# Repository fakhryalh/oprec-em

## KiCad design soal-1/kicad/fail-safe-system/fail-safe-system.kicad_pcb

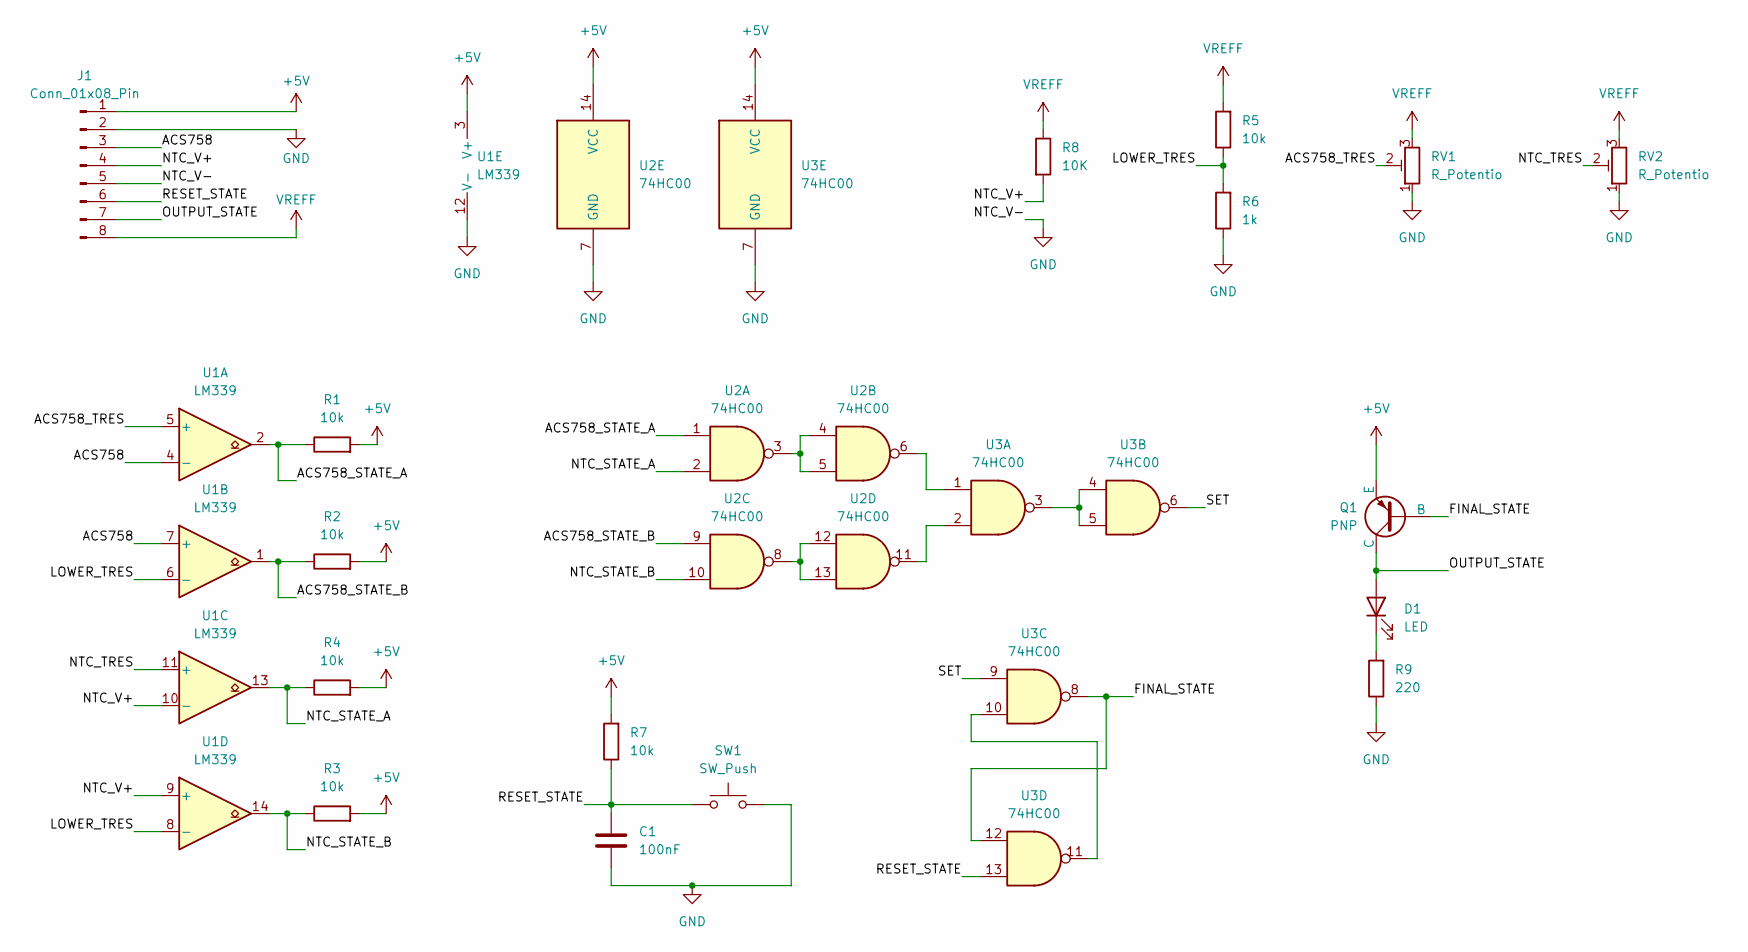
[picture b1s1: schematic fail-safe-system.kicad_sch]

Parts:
C1: 100nF; C_0805_2012Metric_Pad1.18x1.45mm_HandSolder
D1: LED; LED_0805_2012Metric_Pad1.15x1.40mm_HandSolder
J1: Conn_01x08_Pin; PinHeader_1x08_P2.54mm_Vertical
Q1: PNP; SOT-23_Handsoldering
R1, R2, R3, R4, R5, R7: 10k; R_0805_2012Metric_Pad1.20x1.40mm_HandSolder
R6: 1k; R_0805_2012Metric_Pad1.20x1.40mm_HandSolder
R8: 10K; R_0805_2012Metric_Pad1.20x1.40mm_HandSolder
R9: 220; R_0805_2012Metric_Pad1.20x1.40mm_HandSolder
RV1, RV2: R_Potentio; Potentiometer_Bourns_3314G_Vertical
SW1: SW_Push; SW_Push_1P1T_NO_CK_KMR2
U1: LM339; SOIC-14_3.9x8.7mm_P1.27mm
U2, U3: 74HC00; SOIC-14_3.9x8.7mm_P1.27mm

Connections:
+5V: J1.1, Q1.2 (E), R1.2, R2.2, R3.2, R4.2, R7.2, U1.3 (V+), U2.14 (VCC), U3.14 (VCC)
/ACS758: J1.3, U1.4 (-), U1.7 (+)
/ACS758_STATE_A: R1.1, U1.2, U2.1
/ACS758_STATE_B: R2.1, U1.1, U2.9
/ACS758_TRES: RV1.2, U1.5 (+)
/FINAL_STATE: Q1.1 (B), U3.8, U3.12
/LOWER_TRES: R5.1, R6.2, U1.6 (-), U1.8 (-)
/NTC_STATE_A: R4.1, U1.13, U2.2
/NTC_STATE_B: R3.1, U1.14, U2.10
/NTC_TRES: RV2.2, U1.11 (+)
/NTC_V+: J1.4, R8.2, U1.9 (+), U1.10 (-)
/OUTPUT_STATE: D1.2 (A), J1.7, Q1.3 (C)
/RESET_STATE: C1.1, J1.6, R7.1, SW1.1, U3.13
/SET: U3.6, U3.9
GND: C1.2, J1.2, J1.5, R6.1, R9.1, RV1.1, RV2.1, SW1.2, U1.12 (V-), U2.7 (GND), U3.7 (GND)
unnamed: D1.1 (K), R9.2
unnamed: U2.3, U2.4, U2.5
unnamed: U2.6, U3.1
unnamed: U2.11, U3.2
unnamed: U2.8, U2.12, U2.13
unnamed: U3.3, U3.4, U3.5
unnamed: U3.10, U3.11
VREFF: J1.8, R5.2, R8.1, RV1.3, RV2.3

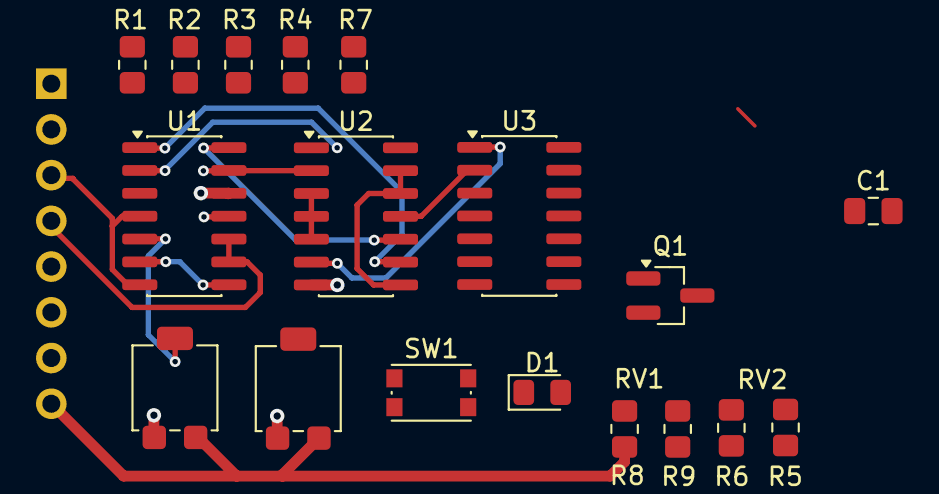
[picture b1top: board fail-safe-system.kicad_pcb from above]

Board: 2 copper layers, 19 parts (1 on the bottom side), 23 nets.

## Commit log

2026-04-16 folder, proteus on soal 1
2026-04-19 add kicad
